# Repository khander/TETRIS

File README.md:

# TETRIS
 v1.0

This is my first big project. For pictrures check the IMAGES folder there are some pictures and vids for you to understand better the idea.
The whole project is written in C++ by me except the music part which is in the bottom of main file.
If you want to check the schematics you can open the KICAD folder.
Also you can notice that there is no top_btn in the code and in schematics as well as the 4x4 matrix. That is because when I finally soldered the project there was some issues with pins.
So eventually to make the project trully finished it is better to take two shifting registers and put plus on them insted of wiring it directly to the controller. Guess that is just rookie mistake though:)
So if you would like to ask smth about code or schematics or anything else feel free to do it. Also every feedback will be appreciated.

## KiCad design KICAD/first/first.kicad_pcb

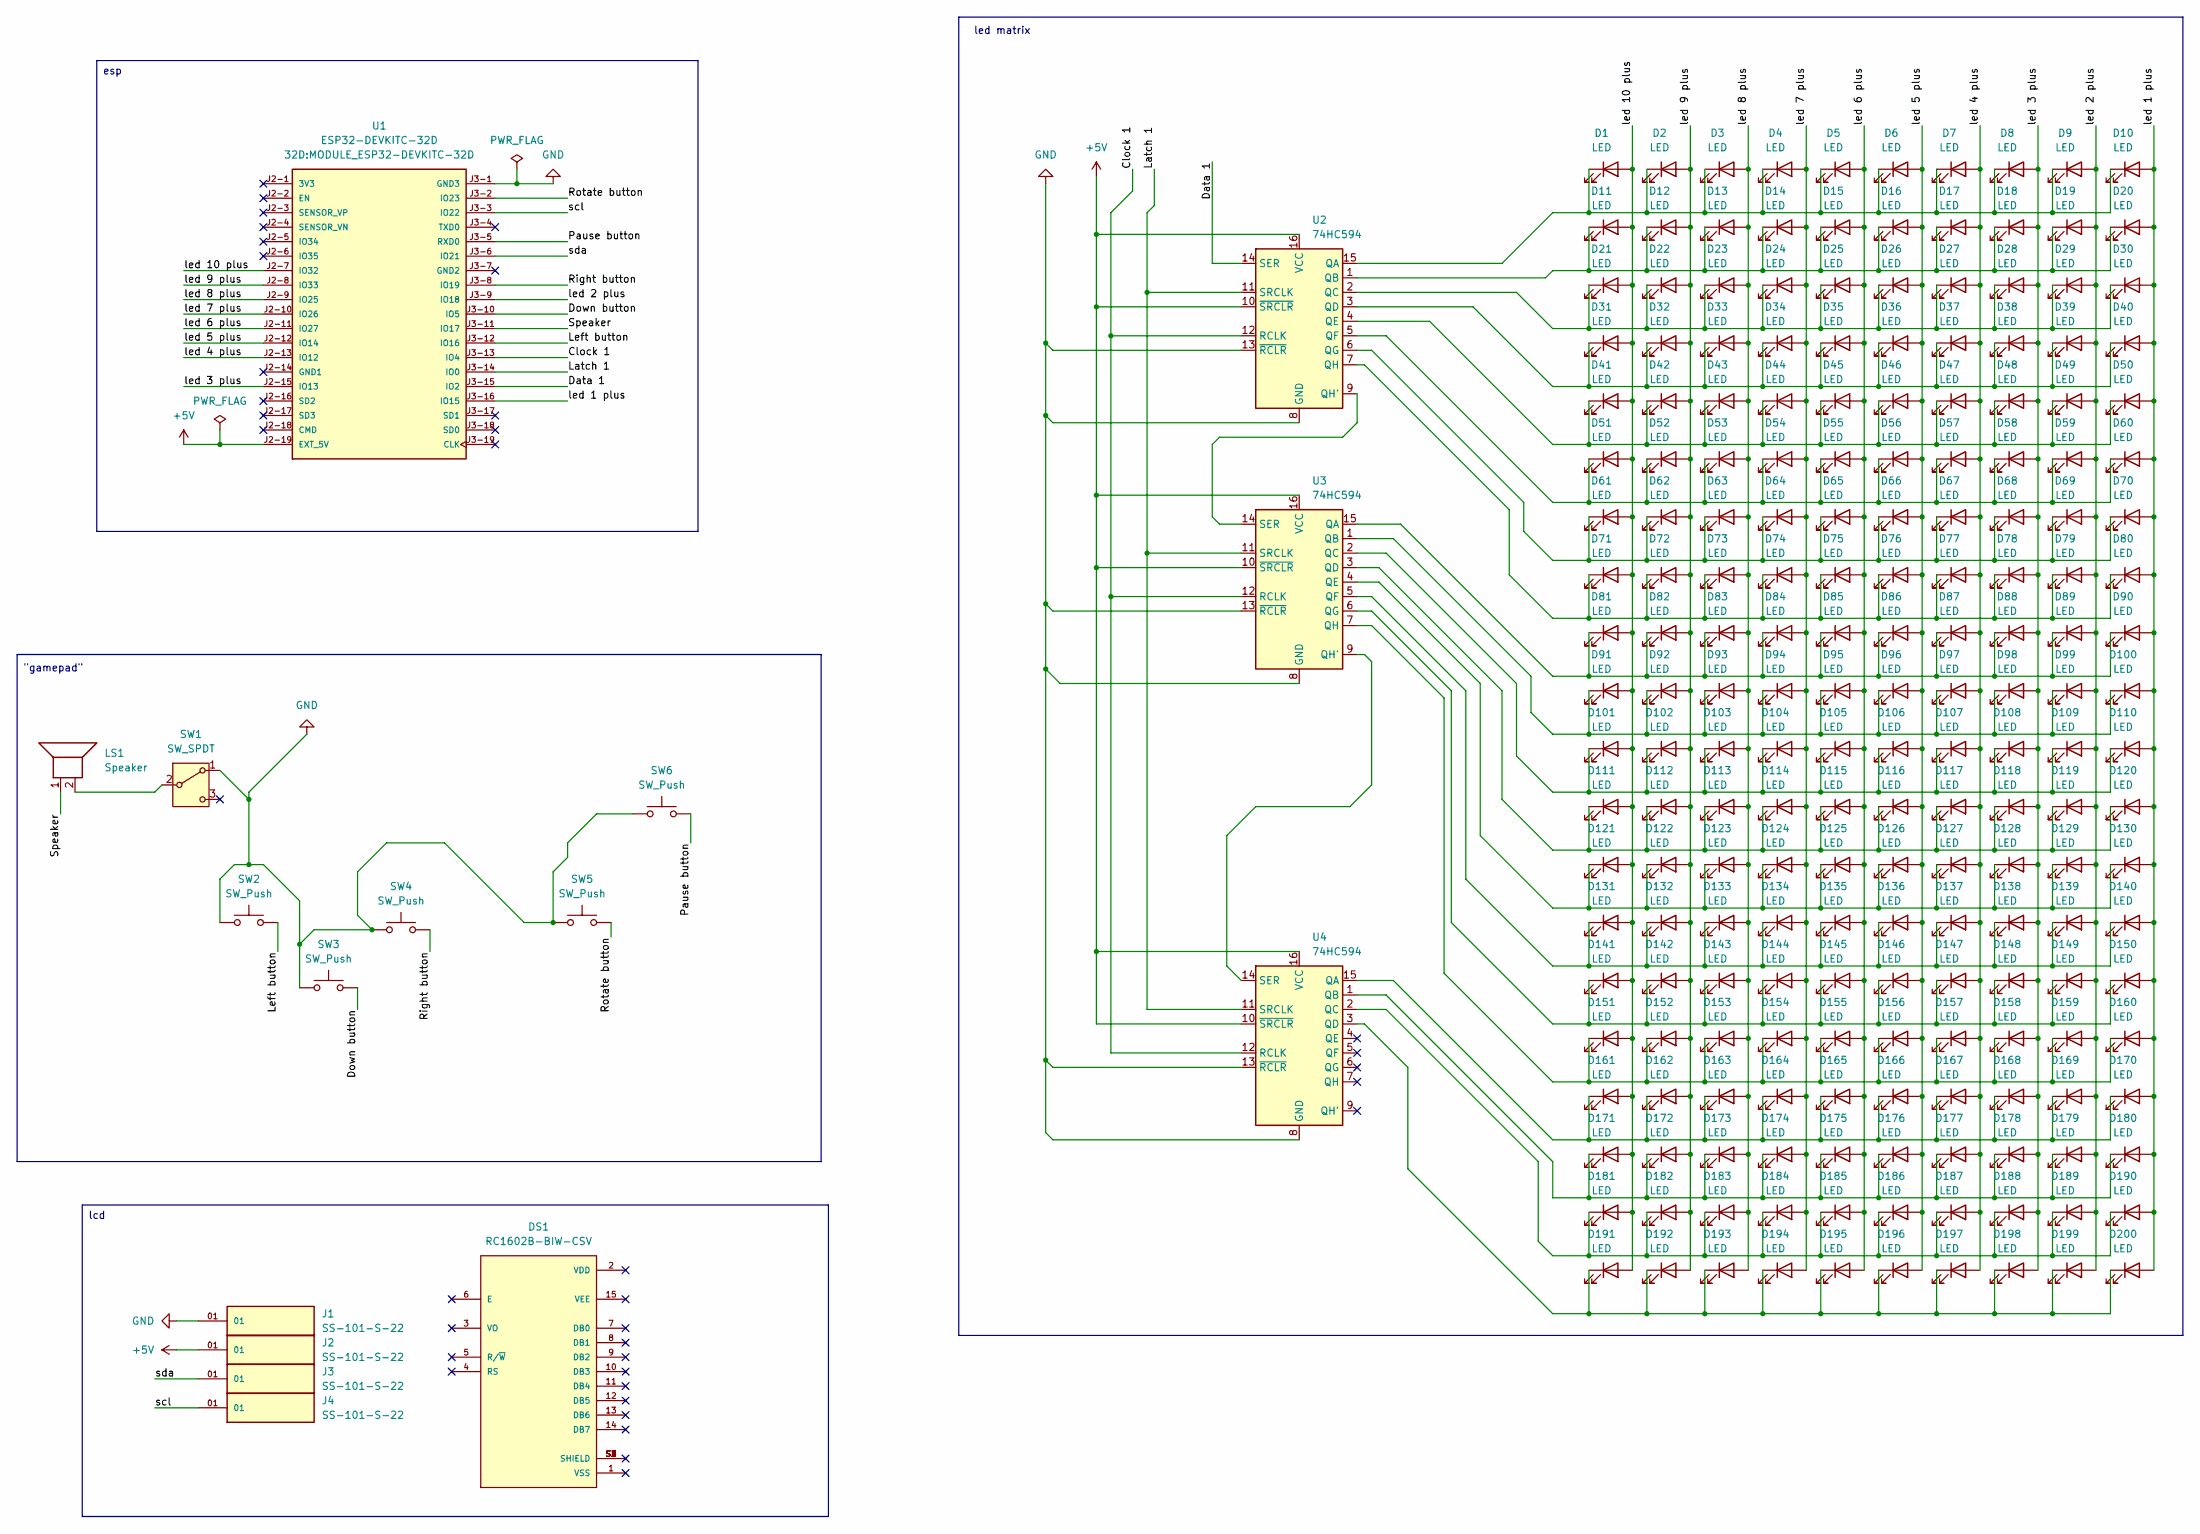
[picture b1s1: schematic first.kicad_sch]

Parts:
D1, D2, D3, D4, D5, D6, D7, D8, D9, D10, D11, D12, D13, D14, D15, D16, D17, D18, D19, D20, D21, D22, D23, D24, D25, D26, D27, D28, D29, D30, D31, D32, D33, D34, D35, D36, D37, D38, D39, D40, D41, D42, D43, D44, D45, D46, D47, D48, D49, D50, D51, D52, D53, D54, D55, D56, D57, D58, D59, D60, D61, D62, D63, D64, D65, D66, D67, D68, D69, D70, D71, D72, D73, D74, D75, D76, D77, D78, D79, D80, D81, D82, D83, D84, D85, D86, D87, D88, D89, D90, D91, D92, D93, D94, D95, D96, D97, D98, D99, D100, D101, D102, D103, D104, D105, D106, D107, D108, D109, D110, D111, D112, D113, D114, D115, D116, D117, D118, D119, D120, D121, D122, D123, D124, D125, D126, D127, D128, D129, D130, D131, D132, D133, D134, D135, D136, D137, D138, D139, D140, D141, D142, D143, D144, D145, D146, D147, D148, D149, D150, D151, D152, D153, D154, D155, D156, D157, D158, D159, D160, D161, D162, D163, D164, D165, D166, D167, D168, D169, D170, D171, D172, D173, D174, D175, D176, D177, D178, D179, D180, D181, D182, D183, D184, D185, D186, D187, D188, D189, D190, D191, D192, D193, D194, D195, D196, D197, D198, D199, D200: LED; LED_D5.0mm
DS1: RC1602B-BIW-CSV; LCD_RC1602B-BIW-CSV; PARTREV N/A
J1, J2, J3, J4: SS-101-S-22; SAMTEC_SS-101-S-22; PARTREV R
LS1: Speaker; Buzzer_12x9.5RM7.6
SW1: SW_SPDT; SW_Slide-03_Wuerth-WS-SLTV_10x2.5x6.4_P2.54mm
SW2, SW3, SW4, SW5, SW6: SW_Push; SW_PUSH-12mm
U1: ESP32-DEVKITC-32D; MODULE_ESP32-DEVKITC-32D; PARTREV V4
U2, U3, U4: 74HC594; SOIC127P600X175-16N

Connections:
+5V: J2.01, U1.J2-19 (EXT_5V), U2.10 (~SRCLR), U2.16 (VCC), U3.10 (~SRCLR), U3.16 (VCC), U4.10 (~SRCLR), U4.16 (VCC)
/Clock 1: U1.J3-13 (IO4), U2.12 (RCLK), U3.12 (RCLK), U4.12 (RCLK)
/Data 1: U1.J3-15 (IO2), U2.14 (SER)
/Down button: SW3.2, U1.J3-10 (IO5)
/Latch 1: U1.J3-14 (IO0), U2.11 (SRCLK), U3.11 (SRCLK), U4.11 (SRCLK)
/Left button: SW2.2, U1.J3-12 (IO16)
/Pause button: SW6.2, U1.J3-5 (RXD0)
/Right button: SW4.2, U1.J3-8 (IO19)
/Rotate button: SW5.2, U1.J3-2 (IO23)
/Speaker: LS1.1, U1.J3-11 (IO17)
/led 1 plus: D10.2 (A), D20.2 (A), D30.2 (A), D40.2 (A), D50.2 (A), D60.2 (A), D70.2 (A), D80.2 (A), D90.2 (A), D100.2 (A), D110.2 (A), D120.2 (A), D130.2 (A), D140.2 (A), D150.2 (A), D160.2 (A), D170.2 (A), D180.2 (A), D190.2 (A), D200.2 (A), U1.J3-16 (IO15)
/led 2 plus: D9.2 (A), D19.2 (A), D29.2 (A), D39.2 (A), D49.2 (A), D59.2 (A), D69.2 (A), D79.2 (A), D89.2 (A), D99.2 (A), D109.2 (A), D119.2 (A), D129.2 (A), D139.2 (A), D149.2 (A), D159.2 (A), D169.2 (A), D179.2 (A), D189.2 (A), D199.2 (A), U1.J3-9 (IO18)
/led 3 plus: D8.2 (A), D18.2 (A), D28.2 (A), D38.2 (A), D48.2 (A), D58.2 (A), D68.2 (A), D78.2 (A), D88.2 (A), D98.2 (A), D108.2 (A), D118.2 (A), D128.2 (A), D138.2 (A), D148.2 (A), D158.2 (A), D168.2 (A), D178.2 (A), D188.2 (A), D198.2 (A), U1.J2-15 (IO13)
/led 4 plus: D7.2 (A), D17.2 (A), D27.2 (A), D37.2 (A), D47.2 (A), D57.2 (A), D67.2 (A), D77.2 (A), D87.2 (A), D97.2 (A), D107.2 (A), D117.2 (A), D127.2 (A), D137.2 (A), D147.2 (A), D157.2 (A), D167.2 (A), D177.2 (A), D187.2 (A), D197.2 (A), U1.J2-13 (IO12)
/led 5 plus: D6.2 (A), D16.2 (A), D26.2 (A), D36.2 (A), D46.2 (A), D56.2 (A), D66.2 (A), D76.2 (A), D86.2 (A), D96.2 (A), D106.2 (A), D116.2 (A), D126.2 (A), D136.2 (A), D146.2 (A), D156.2 (A), D166.2 (A), D176.2 (A), D186.2 (A), D196.2 (A), U1.J2-12 (IO14)
/led 6 plus: D5.2 (A), D15.2 (A), D25.2 (A), D35.2 (A), D45.2 (A), D55.2 (A), D65.2 (A), D75.2 (A), D85.2 (A), D95.2 (A), D105.2 (A), D115.2 (A), D125.2 (A), D135.2 (A), D145.2 (A), D155.2 (A), D165.2 (A), D175.2 (A), D185.2 (A), D195.2 (A), U1.J2-11 (IO27)
/led 7 plus: D4.2 (A), D14.2 (A), D24.2 (A), D34.2 (A), D44.2 (A), D54.2 (A), D64.2 (A), D74.2 (A), D84.2 (A), D94.2 (A), D104.2 (A), D114.2 (A), D124.2 (A), D134.2 (A), D144.2 (A), D154.2 (A), D164.2 (A), D174.2 (A), D184.2 (A), D194.2 (A), U1.J2-10 (IO26)
/led 8 plus: D3.2 (A), D13.2 (A), D23.2 (A), D33.2 (A), D43.2 (A), D53.2 (A), D63.2 (A), D73.2 (A), D83.2 (A), D93.2 (A), D103.2 (A), D113.2 (A), D123.2 (A), D133.2 (A), D143.2 (A), D153.2 (A), D163.2 (A), D173.2 (A), D183.2 (A), D193.2 (A), U1.J2-9 (IO25)
/led 9 plus: D2.2 (A), D12.2 (A), D22.2 (A), D32.2 (A), D42.2 (A), D52.2 (A), D62.2 (A), D72.2 (A), D82.2 (A), D92.2 (A), D102.2 (A), D112.2 (A), D122.2 (A), D132.2 (A), D142.2 (A), D152.2 (A), D162.2 (A), D172.2 (A), D182.2 (A), D192.2 (A), U1.J2-8 (IO33)
/led 10 plus: D1.2 (A), D11.2 (A), D21.2 (A), D31.2 (A), D41.2 (A), D51.2 (A), D61.2 (A), D71.2 (A), D81.2 (A), D91.2 (A), D101.2 (A), D111.2 (A), D121.2 (A), D131.2 (A), D141.2 (A), D151.2 (A), D161.2 (A), D171.2 (A), D181.2 (A), D191.2 (A), U1.J2-7 (IO32)
/scl: J4.01, U1.J3-3 (IO22)
/sda: J3.01, U1.J3-6 (IO21)
GND: J1.01, SW1.1 (A), SW2.1, SW3.1, SW4.1, SW5.1, SW6.1, U1.J3-1 (GND3), U2.8 (GND), U2.13 (~RCLR), U3.8 (GND), U3.13 (~RCLR), U4.8 (GND), U4.13 (~RCLR)
unnamed: D1.1 (K), D2.1 (K), D3.1 (K), D4.1 (K), D5.1 (K), D6.1 (K), D7.1 (K), D8.1 (K), D9.1 (K), D10.1 (K), U2.15 (QA)
unnamed: D11.1 (K), D12.1 (K), D13.1 (K), D14.1 (K), D15.1 (K), D16.1 (K), D17.1 (K), D18.1 (K), D19.1 (K), D20.1 (K), U2.1 (QB)
unnamed: D21.1 (K), D22.1 (K), D23.1 (K), D24.1 (K), D25.1 (K), D26.1 (K), D27.1 (K), D28.1 (K), D29.1 (K), D30.1 (K), U2.2 (QC)
unnamed: D31.1 (K), D32.1 (K), D33.1 (K), D34.1 (K), D35.1 (K), D36.1 (K), D37.1 (K), D38.1 (K), D39.1 (K), D40.1 (K), U2.3 (QD)
unnamed: D41.1 (K), D42.1 (K), D43.1 (K), D44.1 (K), D45.1 (K), D46.1 (K), D47.1 (K), D48.1 (K), D49.1 (K), D50.1 (K), U2.4 (QE)
unnamed: D51.1 (K), D52.1 (K), D53.1 (K), D54.1 (K), D55.1 (K), D56.1 (K), D57.1 (K), D58.1 (K), D59.1 (K), D60.1 (K), U2.5 (QF)
unnamed: D61.1 (K), D62.1 (K), D63.1 (K), D64.1 (K), D65.1 (K), D66.1 (K), D67.1 (K), D68.1 (K), D69.1 (K), D70.1 (K), U2.6 (QG)
unnamed: D71.1 (K), D72.1 (K), D73.1 (K), D74.1 (K), D75.1 (K), D76.1 (K), D77.1 (K), D78.1 (K), D79.1 (K), D80.1 (K), U2.7 (QH)
unnamed: D81.1 (K), D82.1 (K), D83.1 (K), D84.1 (K), D85.1 (K), D86.1 (K), D87.1 (K), D88.1 (K), D89.1 (K), D90.1 (K), U3.15 (QA)
unnamed: D91.1 (K), D92.1 (K), D93.1 (K), D94.1 (K), D95.1 (K), D96.1 (K), D97.1 (K), D98.1 (K), D99.1 (K), D100.1 (K), U3.1 (QB)
unnamed: D101.1 (K), D102.1 (K), D103.1 (K), D104.1 (K), D105.1 (K), D106.1 (K), D107.1 (K), D108.1 (K), D109.1 (K), D110.1 (K), U3.2 (QC)
unnamed: D111.1 (K), D112.1 (K), D113.1 (K), D114.1 (K), D115.1 (K), D116.1 (K), D117.1 (K), D118.1 (K), D119.1 (K), D120.1 (K), U3.3 (QD)
unnamed: D121.1 (K), D122.1 (K), D123.1 (K), D124.1 (K), D125.1 (K), D126.1 (K), D127.1 (K), D128.1 (K), D129.1 (K), D130.1 (K), U3.4 (QE)
unnamed: D131.1 (K), D132.1 (K), D133.1 (K), D134.1 (K), D135.1 (K), D136.1 (K), D137.1 (K), D138.1 (K), D139.1 (K), D140.1 (K), U3.5 (QF)
unnamed: D141.1 (K), D142.1 (K), D143.1 (K), D144.1 (K), D145.1 (K), D146.1 (K), D147.1 (K), D148.1 (K), D149.1 (K), D150.1 (K), U3.6 (QG)
unnamed: D151.1 (K), D152.1 (K), D153.1 (K), D154.1 (K), D155.1 (K), D156.1 (K), D157.1 (K), D158.1 (K), D159.1 (K), D160.1 (K), U3.7 (QH)
unnamed: D161.1 (K), D162.1 (K), D163.1 (K), D164.1 (K), D165.1 (K), D166.1 (K), D167.1 (K), D168.1 (K), D169.1 (K), D170.1 (K), U4.15 (QA)
unnamed: D171.1 (K), D172.1 (K), D173.1 (K), D174.1 (K), D175.1 (K), D176.1 (K), D177.1 (K), D178.1 (K), D179.1 (K), D180.1 (K), U4.1 (QB)
unnamed: D181.1 (K), D182.1 (K), D183.1 (K), D184.1 (K), D185.1 (K), D186.1 (K), D187.1 (K), D188.1 (K), D189.1 (K), D190.1 (K), U4.2 (QC)
unnamed: D191.1 (K), D192.1 (K), D193.1 (K), D194.1 (K), D195.1 (K), D196.1 (K), D197.1 (K), D198.1 (K), D199.1 (K), D200.1 (K), U4.3 (QD)
unnamed: LS1.2, SW1.2 (B)
unnamed: U2.9 (QH'), U3.14 (SER)
unnamed: U3.9 (QH'), U4.14 (SER)

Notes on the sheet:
lcd
esp
led matrix
"gamepad"

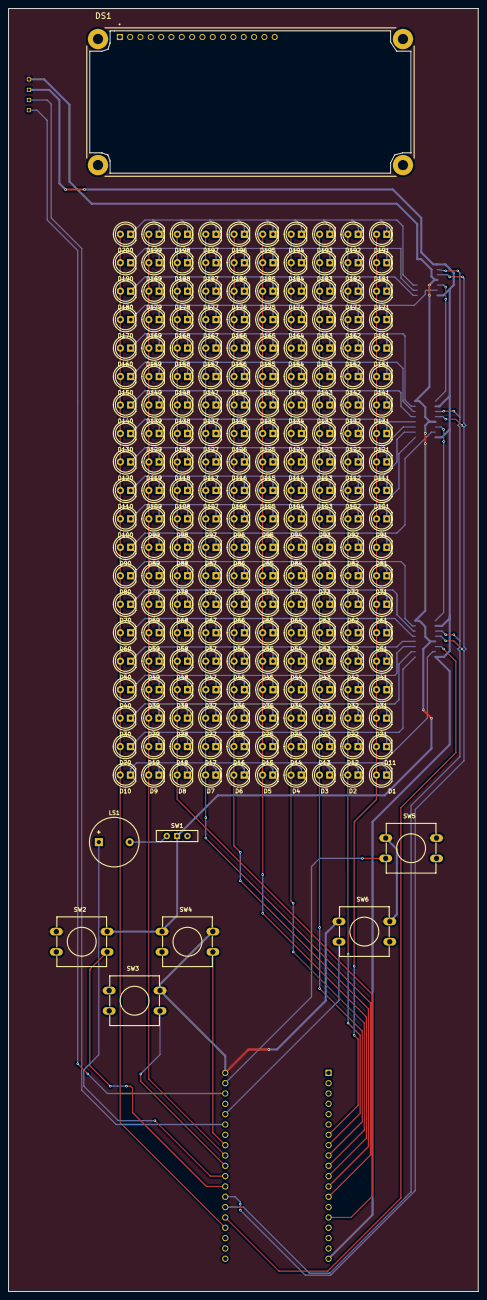
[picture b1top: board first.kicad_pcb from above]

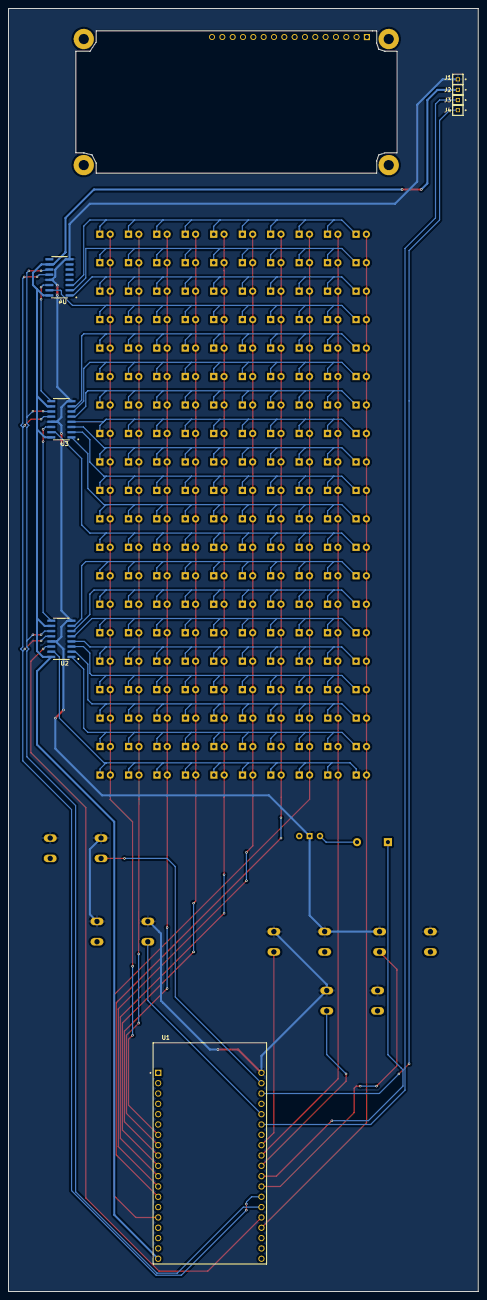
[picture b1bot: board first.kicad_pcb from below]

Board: 2 copper layers, 115.5 x 315.5 mm, 216 parts (8 on the bottom side), 46 nets.

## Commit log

2024-06-15 correct figures fall
2024-06-15 rotate, left, right moves with buttons and special tickrate
2024-06-15 lcd display added
2024-06-26 lcd file - not finished
2024-07-14 lcd display added everything is connected but 4x4 matrix need to be checked -> ready for final soldering
2024-08-22 soldering finished
2024-08-22 fixed: -figures getting out of visible matrix at the edges after rotating -i_figure became 3 parts(not 4) after rotating -figures layering on the figures put in matrix while moving to left/right
2024-08-24 correct buttons output with long press to do: fix the bug with down button
2024-08-24 correct buttons long press fix: down button bug
2024-08-30 bug fixed: down button
2024-09-01 added: delete rows(up to 4) rows that was upper than deleted falls down
2024-09-01 random figues fall increased down button speed while pressed to do: score and level system
2024-09-01 lcd bagan: hello page start(pause) button added
2024-09-02 pause btn added
2024-09-03 added score counting to do: write function for high_score save(flash memory 1 byte...) to do: add level counting(10 rows = 1 level)
2024-09-03 score - done to do: manage difficulty levels to do: add music to do: make the next figure reveal
2024-09-04 correct score counting level difficulty managed
2024-09-04 music added to do: add next figure reveal
2024-09-05 final commit fixed some minor bugs added KiCad schematic README file will be added soon v1.0 - RELEASED :)
2024-09-07 videos
2025-03-18 kicad schematic changed. pcb creation started
    led matrix done, some registers wired
2025-03-20 pcb finished
    add some holes for case to be attached
